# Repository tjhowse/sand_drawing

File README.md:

# Huh?

So you've been reading about all the benefits of this "mindfulness" thing and you want to give it a try.
You do some research and learn it requires "meditation", "introspection" and other kinds of tedious woo.
Who has time for that? It's {current_year} for christ's sake! I don't want a tiny tray of rocks and sand
on my desk to rake around. Surely there's some turn-key solution to this problem already.

That's what this project is for. Outsource responsibility for an ordered mind to make more time for the important things, like computer games. And croissants.

# Oh

This project (will contain/contains) all the knowledge you will need to build your own sand drawing robot. Heavily inspired by the likes of [Sandsara](https://www.kickstarter.com/projects/edcano/sandsara) and [Sisyphus](https://sisyphus-industries.com/). It's a robot that moves a ball around in a bed of sand to draw cool patterns. The patterns can be updated via wifi, and it can cycle through them, you can create your own, etc, etc. This project is open source, cheap, and hopefully as easy as possible to build.

# Building it

## Skills required

This isn't a Lego set. You'll need to have access to the following skills:

* Basic woodworking,
* Intermediate soldering,
* Following technical instructions,
* Drilling a hole sideways through steel rod,
* Recovering from setbacks.

I'll do my best to make the instructions as comprehensive and comphrehensible as I can. I appreciate any and all feedback.

## Videos

[Playlist on Youtube.](https://www.youtube.com/playlist?list=PLT7ckgz8vcoY2YFqqQTA0kUofwehtqQul) Maybe worth watching.

## PCB

The PCB is quite simple and cheap. PCBWay generously sponsored a production run of the v1.2 PCBs and they came out perfect. You can order the PCB using [this link](https://www.pcbway.com/project/shareproject/Sand_Drawing_Robot_control_board_344d0ab2.html) and I'll get a small cut. PCBWay asked me to review the board in a youtube video and link it in the readme, but required no further quid pro quo.

## Build logs

For now the build logs are on [my wiki](https://wiki.tjhowse.com/doku.php?id=projects:sand_drawing:overview). Over time they'll morph into actual instructions and end up in this repo.

## Bill of materials

None of these parts are particularly hard to find. Check ebay and whatnot. Try to buy local if you can. It's hard to guess how much it will all cost in total, but I've tried to design everything to be as economical as possible. Excluding the housing I would (very roughly) estimate the BoM to come out to around AUD$200. The housing could be as cheap as AUD$50 (Melamine board, polycarbonate) or as expensive as you want, with lacquered hardwood and tempered glass.

    These bills of material are slightly out of date. Consult the youtube videos.

### Mechanical
| Item | Type | Count | Note |
| ---- | ---- | ----- | ---- |
| Laser cut parts | Various | Many | The current best solution is made from 3mm laser cut plywood. A 3D printed variant is quite possible. |
| Stepper pulley | GT2-20, 12.35mm high | 2 | My steppers had pulleys from the factory. |
| Belt | S2M belt 120mm | 2 | S2M ≈ GT2. |
| Belt | S2M belt 278mm | 1 | |
| Shaft 1 | 8mm x 90mm | 1 | Mild steel is easier to cross-drill than stainless. |
| Shaft 2 | 8mm x 33mm | 1 | |
| Bearing | 608 | 6 | Cheap skate bearings are fine. |
| Washers | 8mm ID, 15.7mm OD | 5 | OD not critical, but it must not rub on outer race of bearings. |
| Washers | 3mm ID, 6.8mm OD | 12 | |
| Bolts | M3x12mm | 8 | I used all 20mm and cut them to length. |
| Bolts | M3x20mm | 2 | |
| Nylock nuts | M3 | 2 | Nylock not critical. |
| Pins | 2mm diameter | 5 | Roll pins would be best, I used nails. +1 extra for pinning shaft 1 into the bearings. |
| Magnets | 12mm diameter, 2mm high neodymium | 2-4 | Situational dimensions. Get a variety of sizes to aid experimentation. |
| Cable ties | 200mm x 4.6mm Nylon | 2 | Dimensions not critical. |

### Electrical
| Item | Type | Count | Note |
| ---- | ---- | ----- | ---- |
| Microcontroller | ESP-WROOM-32D | 1 | Wifi and bluetooth built-in |
| Stepper motor | NEMA-17 | 2 | 200 steps/revolution, around 40mm long, at least 30 N.cm of holding torque. It's not critical, really. |
| Stepper driver | Pololu pinout | 2 | A4988, DRV8825 or TMC2100 in [increasing order of preference](https://github.com/tjhowse/sand_drawing/issues/6) |
| PCB | Custom made | 1 | The design is [here](./pcb/sand_drawing). It's easier and cheaper to have one made than you [might imagine](./pcb/sand_drawing/README_PCB.md).
| Hall effect sensors | SS49E | 2 | Used for detecting arm position. |
| PSU | 12v DC 1A | 1 | A wall wart should be fine. |
| Stepper driver socket | 16x1 2.54mm female | 2 | https://au.rs-online.com/web/p/pcb-sockets/2304893/ |
| Stepper motor socket | 4x1 3.5mm | 2 | https://au.rs-online.com/web/p/pcb-headers/8971039/ |
| Stepper motor plug | 4x1 3.5mm | 2 | https://au.rs-online.com/web/p/pcb-terminal-blocks/8971004/ |
| Optoswitch socket | 3x1 3.5mm | 2 | https://au.rs-online.com/web/p/pcb-headers/8971020/ |
| Optoswitch plug | 3x1 3.5mm | 2 | https://au.rs-online.com/web/p/pcb-terminal-blocks/8971001/ |
| Power socket | 2x1 3.5mm | 1 | https://au.rs-online.com/web/p/pcb-headers/8971026/ |
| Power plug | 2x1 3.5mm | 1 | https://au.rs-online.com/web/p/pcb-terminal-blocks/8970998/ |
| Buttons | 6mm | 2 | https://au.rs-online.com/web/p/tactile-switches/1359534/ |
| UART Header | 3x1 2.54mm male | 1 | https://au.rs-online.com/web/p/pcb-headers/8967364/ |
| 12VDC Barrel socket | 2.1mm pin | 1 | https://au.rs-online.com/web/p/dc-power-sockets/0448370/ |

### Enclosure
| Item | Type | Count | Note |
| ---- | ---- | ----- | ---- |
| Base | Wooood? | 1 | Holds the steppers and circuitry. |
| Top | Wooood? | 1 | Any convex polygon should work. |
| Bed | Glass? | 1 | |
| Lid | Glass | 1 | |
| Sand | Sand | 31378908 | < 100 μm grains, dry.

# Flashing

To flash the software onto the ESP32 you'll need to use the provided scripts `flash32.sh` and `write32.sh`. You'll have to update them with the current version of micropython and the device name of your serial port adapter. When flashing micropython you'll need to hold down the IO0 button while connecting power, then release it five or so seconds after powering on. You can then run `flash32.sh` and it'll write the "OS" onto the chip. Then you can repower again and run `write32.sh` to load the project's scripts onto the board.

# Communication
The ESP-WROOM-32 has wifi and BLE built in. Currently the robot connects to a wifi network, then an MQTT server, to receive commands. Bluetooth should also be possible in the future.

## MQTT Topics
There are a few topics that the robot listens to. Each topic starts with `{secrets.mqtt_root}/sand_drawing/`. I suggest you publish patterns/generators with the retain bit so the robot starts up and then begins that pattern.
| Topic | Example payload | Description |
| ----  | ------- | ----------- |
| `pattern` | `G28 X,G28 Y,G1 X0 Y175,G1 X123 Y123,G1 X175 Y0,J0 2` | Starts drawing the pattern defined by the GCODE in the payload. |
| `generator` | [Here](./pub_gen.py#L82) | Starts drawing the pattern defined by the generator in the payload. See below for details on generators. |
| `save_generator` | `1.pat {generator string}` | Saves the generator to a file in the robot's flash storage. The file extension must be `.pat`. A blank string will erase the generator. |
| `run_generator` | `1.pat` | Starts drawing the previously saved generators. |
| `delete_generator` | `1.pat` | Deletes a generator saved to the robot. |
| `list_generators` | N/A | Publishes a list of filenames to `generator_list` topic. |
| `shuffle_generators` | `3600` | Randomly picks a saved generator and starts drawing it. Optionally provide a number of seconds before choosing another random generator |

# Configuration
There are some files you'll need to edit before your robot will work for you, probably.
[#TODO populate this section.](https://github.com/tjhowse/sand_drawing/issues/13)

# Pattern definition
There are currently two ways to design patterns for the robot.

## GCODEs
This is a sequence of coordinates that define the path of the ball, as well as changing modes and looping. The following GCODES are currently supported. GCODES are separated by a comma.

| Name | GCODE | Example | Description |
| ---- | ----- | ------- | ----------- |
| Home axis| G28 | `G28 X,G28 Y,` | Home either the X or Y axis. Any command that needs an absolute position reference will fail unless both axes have been homed first. |
| Move | G1 | `G1 X10 Y50 S100,` | Go to the X and Y coordinates specified at 100mm/s. Currently the [speed field is ignored](https://github.com/tjhowse/sand_drawing/issues/4). The G1 movement mode carefully tracks every step and should be perfectly accurate if your steppers do not slip. |
| Fast move | G0 |  `G0 X10 Y50 S100,` | Same as G1 however the step signal square wave is generated using PWM so some resolution is lost. At time of writing it is not well-supported. It's really fast though. |
| Coordinate mode | G16 | `G16 0,` | This setting is used to control the interpretation of the `X` and `Y` parameters in the G0 and G1 commands. `0`: Raw speed, `1`: Raw angle, `2`: Cartesian (Default), `3`: Polar (unimplemented) |
| Jump | J0 | `J0 3,` | This jumps to the specified line in the GCODE-defined pattern. Used for creating loops. |
| Absolute coordinate mode | G90 | `G90` | Puts the robot into absolute movement mode. Coordinates in G0/G1 commands are interpreted as absolute position references. (Default) |
| Relative coordinate mode | G91 | `G91` | Puts the robot into relative movement mode. Coordinates in G0/G1 commands are interpreted as movement vectors from the previous position. |

## Generators
You can define a pattern using a python generator function. [Examples here](./pub_gen.py). This is probably the best option for non-trivial patterns.

### Tread lightly
Keep the target hardware in mind when writing generators. It's very resource-constrained. Try to limit RAM usage, and think hard before `import`ing anything. There are some [helper functions](./generator_libs.py) and [constants](./constants.py) in-scope that you can use.

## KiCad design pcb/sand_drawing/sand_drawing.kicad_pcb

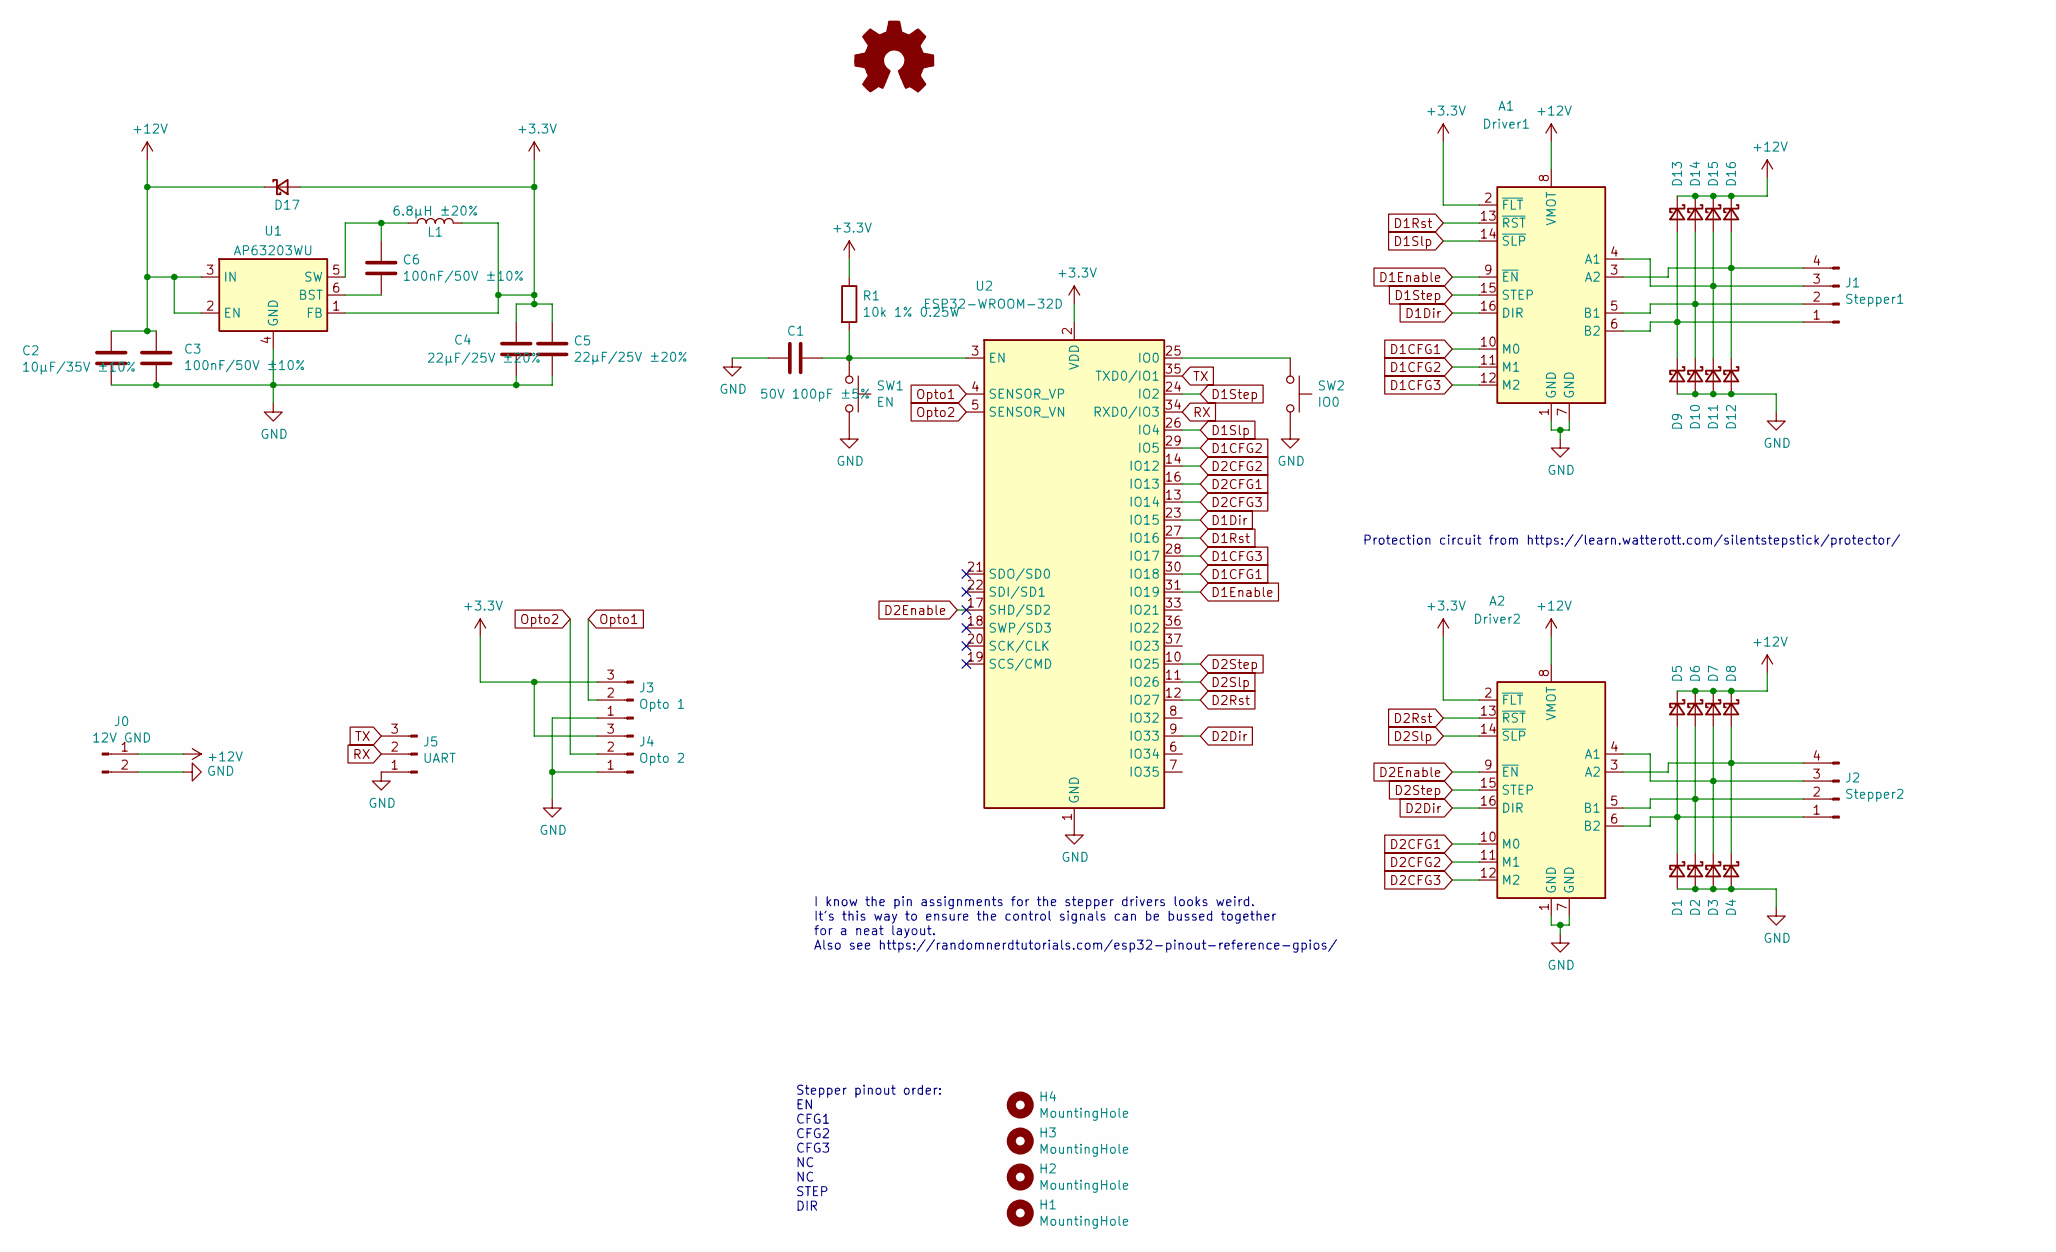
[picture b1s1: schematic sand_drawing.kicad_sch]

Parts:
A1: Driver1; Pololu_Breakout-16_15.2x20.3mm
A2: Driver2; Pololu_Breakout-16_15.2x20.3mm
C1: 50V 100pF ±5%; C_0805_2012Metric; MPN CL21C101JBANNNC; LCSC C1790
C2: 10µF/35V ±10%; C_1206_3216Metric; MPN CGA5L1X7R1V106K160AE; LCSC C15850
C3, C6: 100nF/50V ±10%; C_0603_1608Metric; MPN CGA3E2X7R1H104K080AA; LCSC C15850
C4, C5: 22µF/25V ±20%; C_1206_3216Metric; MPN C3216X5R1E226M160AB; LCSC C15850
D1, D2, D3, D4, D5, D6, D7, D8, D9, D10, D11, D12, D13, D14, D15, D16, D17: 100V 850mV@2A Schottky Diode; D_SMB; MPN Taiwan Semiconductor SS210; LCSC C14996
H1, H2, H3, H4: MountingHole; MountingHole_3.2mm_M3
J0: 12V GND; PhoenixContact_MCV_1,5_2-G-3.5_1x02_P3.50mm_Vertical
J1: Stepper1; PhoenixContact_MCV_1,5_4-G-3.5_1x04_P3.50mm_Vertical
J2: Stepper2; PhoenixContact_MCV_1,5_4-G-3.5_1x04_P3.50mm_Vertical
J3: Opto 1; PhoenixContact_MCV_1,5_3-G-3.5_1x03_P3.50mm_Vertical
J4: Opto 2; PhoenixContact_MCV_1,5_3-G-3.5_1x03_P3.50mm_Vertical
J5: UART; PinSocket_1x03_P2.54mm_Vertical
L1: 6.8µH ±20%; WURTH_6060; MPN Wurth 74439346068
LOGO1: Logo_Open_Hardware_Small; OSHW-Logo2_14.6x12mm_SilkScreen
R1: 10k 1% 0.25W; R_0603_1608Metric; MPN CRGP0603F10K; LCSC C25804
SW1: EN; SW_PUSH_6mm
SW2: IO0; SW_PUSH_6mm
U1: AP63203WU; TSOT-26-6; MPN AP63203WU-7
U2: ESP32-WROOM-32D; ESP32-WROOM-32; MPN ESP32-WROOM-32D

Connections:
+3V3: A1.2 (~FLT), A2.2 (~FLT), C4.1, C5.1, D17.2 (A), J3.3, J4.3, L1.2, R1.1, U1.1 (FB), U2.2 (VDD)
+12V: A1.8 (VMOT), A2.8 (VMOT), C2.1, C3.1, D5.1 (K), D6.1 (K), D7.1 (K), D8.1 (K), D13.1 (K), D14.1 (K), D15.1 (K), D16.1 (K), D17.1 (K), J0.1, U1.2 (EN), U1.3 (IN)
D1CFG1: A1.10 (M0), U2.30 (IO18)
D1CFG2: A1.11 (M1), U2.29 (IO5)
D1CFG3: A1.12 (M2), U2.28 (IO17)
D1Dir: A1.16 (DIR), U2.23 (IO15)
D1Enable: A1.9 (~EN), U2.31 (IO19)
D1Rst: A1.13 (~RST), U2.27 (IO16)
D1Slp: A1.14 (~SLP), U2.26 (IO4)
D1Step: A1.15 (STEP), U2.24 (IO2)
D2CFG1: A2.10 (M0), U2.16 (IO13)
D2CFG2: A2.11 (M1), U2.14 (IO12)
D2CFG3: A2.12 (M2), U2.13 (IO14)
D2Dir: A2.16 (DIR), U2.9 (IO33)
D2Enable: A2.9 (~EN), U2.17 (SHD/SD2)
D2Rst: A2.13 (~RST), U2.12 (IO27)
D2Slp: A2.14 (~SLP), U2.11 (IO26)
D2Step: A2.15 (STEP), U2.10 (IO25)
GND: A1.1 (GND), A1.7 (GND), A2.1 (GND), A2.7 (GND), C1.2, C2.2, C3.2, C4.2, C5.2, D1.2 (A), D2.2 (A), D3.2 (A), D4.2 (A), D9.2 (A), D10.2 (A), D11.2 (A), D12.2 (A), J0.2, J3.1, J4.1, J5.1, SW1.2, SW2.2, U1.4 (GND), U2.1 (GND), U2.15 (GND), U2.38 (GND), U2.39 (GND)
unnamed: A1.4 (A1), D11.1 (K), D15.2 (A), J1.3
unnamed: A1.3 (A2), D12.1 (K), D16.2 (A), J1.4
unnamed: A1.5 (B1), D10.1 (K), D14.2 (A), J1.2
unnamed: A1.6 (B2), D9.1 (K), D13.2 (A), J1.1
unnamed: A2.4 (A1), D3.1 (K), D7.2 (A), J2.3
unnamed: A2.3 (A2), D4.1 (K), D8.2 (A), J2.4
unnamed: A2.5 (B1), D2.1 (K), D6.2 (A), J2.2
unnamed: A2.6 (B2), D1.1 (K), D5.2 (A), J2.1
unnamed: C6.2, U1.6 (BST)
unnamed: C6.1, L1.1, U1.5 (SW)
unnamed: C1.1, R1.2, SW1.1, U2.3 (EN)
unnamed: SW2.1, U2.25 (IO0)
Opto1: J3.2, U2.4 (SENSOR_VP)
Opto2: J4.2, U2.5 (SENSOR_VN)
RX: J5.2, U2.34 (RXD0/IO3)
TX: J5.3, U2.35 (TXD0/IO1)

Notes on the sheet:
Protection circuit from https://learn.watterott.com/silentstepstick/protector/
I know the pin assignments for the stepper drivers looks weird. It's this way to ensure the control signals can be bussed together for a neat layout. Also see https://randomnerdtutorials.com/esp32-pinout-reference-gpios/
Stepper pinout order: EN CFG1 CFG2 CFG3 NC NC STEP DIR

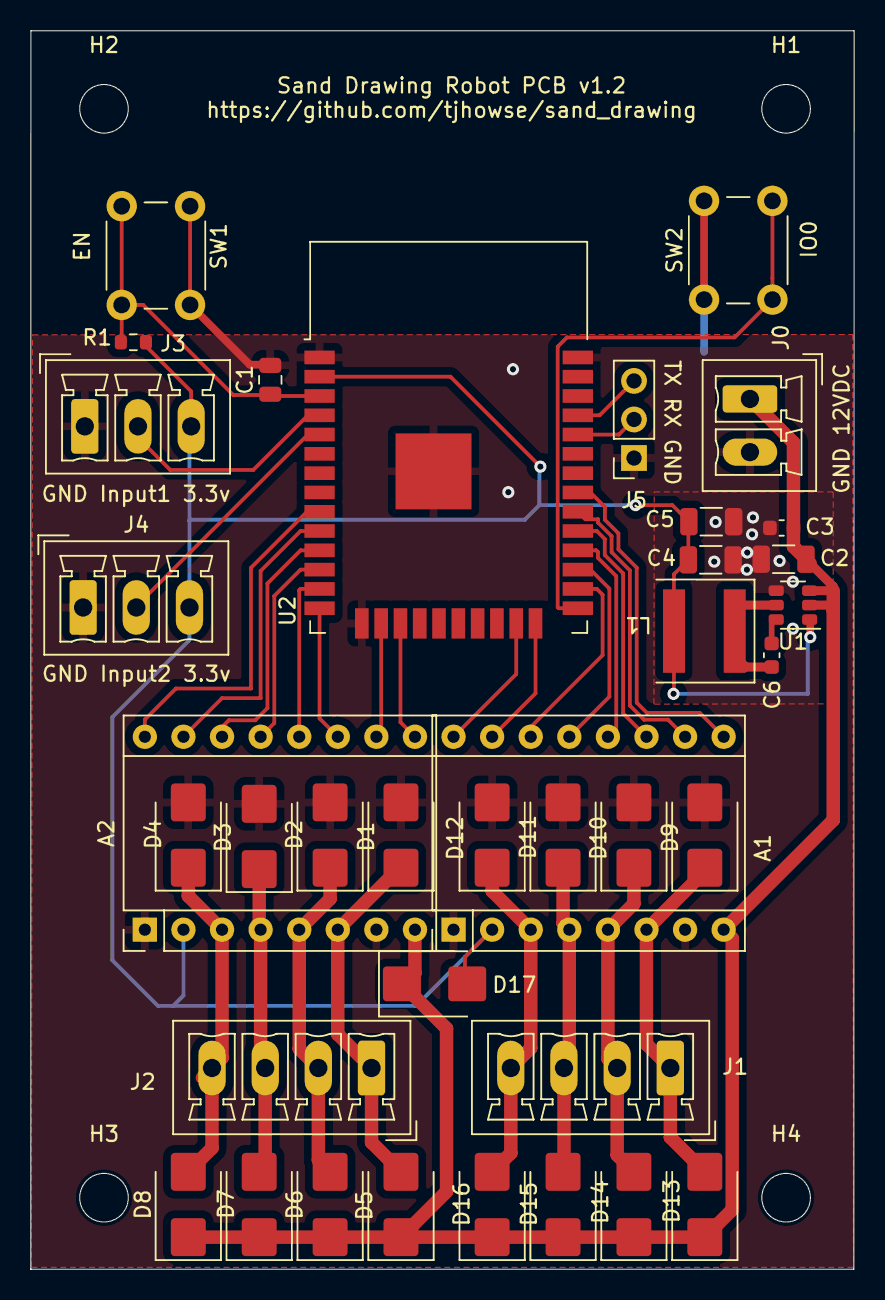
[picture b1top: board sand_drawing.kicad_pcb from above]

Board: 2 copper layers, 54.2 x 81.5 mm, 41 parts (0 on the bottom side), 35 nets.

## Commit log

2020-04-12 More working.
2020-04-12 Add readme, and something else I don't remember.
2020-04-13 Add arm1
2020-04-13 Add a link to the belt length calculator.
2020-04-13 Fix whitespace
2020-04-13 Starting the framework for the code.
2020-04-13 Add a guide to the other side shaft 1 drive gear.
2020-04-13 Fix the split on arm1
    Add shaft 2 driven pulley
2020-04-13 Add bottom bearing mount stuff.
2020-04-14 Make arm slots work better.
2020-04-14 Add framework for mqtt stuff.
2020-04-14 Add gitignore to exclude changes to secrets.py
2020-04-14 Add basic framework for testing steppers.
2020-04-15 Move real secrets to secrets_real.py so I don't accidentally check in my secrets.
2020-04-15 Beef up lip on shaft 2 driven pulley.
    Add arm2
2020-04-15 Add license.
2020-04-15 Start thinking about proper stepper driving.
2020-04-15 Add an assembled view.
    Add optoflags and an optoswitch holder.
2020-04-16 Tweak for printing.
2020-04-16 Add PCB design. Not routed yet.
2020-04-17 Add jumpers for microstepping.
2020-04-17 Rearrange stuff, start routing.
2020-04-18 More traces
2020-04-18 Add flood fills.
    Add silkscreen text for spare pins.
2020-04-18 Tidy up schematic.
2020-04-18 Tweaks.
2020-04-18 Add the basics of some stepper control. Still not working perfectly.
2020-04-19 Rework interval maths.
2020-04-19 Bulk hacking. Home one axis at a time for now.
2020-04-19 Added loads.
2020-04-19 Add debug
    Fix multi-axis movement
    Add easy toggle for wild mode.
2020-04-19 Add debug mode flag for printing debug messages.
2020-04-19 Rotate pin holding arm1 to shaft1 to allow it to be tapped through.
2020-04-19 Fix GH issue #2 by splitting arm1 horizontally not vertically.
2020-04-19 Use the split version of arm1 in the assembled module.
2020-04-21 Lots of float squashing. More debugging. Less debugging sometimes.
2020-04-21 Add receiving patterns from MQTT!
    It only loads a new pattern on stepping between instructions. So patterns with long-lived steps, such as raw relative moves that continue forever, new patterns will never be loaded.
2020-04-23 Working on adding support for an esp32-based device.
2020-04-23 Add a flag to disable MQTT checking, and check for new patterns on a timer.
2020-04-23 Break the PWM stepping out to a setting separate to the microcontroller. This code gets 3.7s revolutions on an ep32.
2020-04-25 Removed the program-wide PWM stepping setting in favour of G0 - Fast move gcode.
    Not fully implemented yet.
2020-04-25 Some refactoring, spam prevention, etc.
2020-04-25 Track index on G0 moves. First test showed this doesn't work quite right.
2020-04-25 Working on handling fast movements overshooting their target by good margins.
2020-04-25 Shockingly broken in most ways.
2020-04-26 Working on stopping a fast move at an ideal point. Not quite there.
2020-05-04 Testing new patterns with DRV8825 stepper drivers.
2020-05-04 Mod 360 the angle to set_angle.
2020-05-04 Split project into multiple files for ease of navigation.
2020-05-04 Working on the kinematics stuff.
2020-05-04 Refactor complete.
2020-05-04 Cartesian mode working, somewhat.
2020-05-05 Working finding the other kinematic solution.
2020-05-05 Finish calculating the most direct movement path between the current and desired position.
2020-05-06 Add logic to slow down arm1 to match the max move speed of arm2.
2020-05-06 Handle the zero case
2020-05-06 Notes on speed calculation, tweaks.
2020-05-06 Better differential speed compensation for cartesian moves. Not perfect yet.
2020-05-10 Added arm2optoarm for homing Y axis.
2020-05-11 Made arm2 a bit thinner to give more clearance for the arm2 opto.
2020-05-12 Allow to home to indicies other than 0.
2020-05-12 Beginning to work on the bounds-limiting code to stop the arm hitting the sides of the enclosure.
    This doesn't work yet. I've added test_coordinate_bounds.py to check things out off-board.
2020-05-12 add a few more test cases.
2020-05-12 Handle import failure better when running off-target.
    Fix demo case.
2020-05-12 Fix closest two points calculation.
2020-05-12 :thonking:
2020-05-12 Remove debugging and truncate filtered coordinates.
2020-05-12 On second thoughts, let's not. That might cause weird stepping along the edges.
2020-05-12 Use the new code to limit the coordinates.
2020-05-12 Fix arm length, fine-tune homing index zero points.
2020-05-12 Add TODO.
2020-05-12 Add resource for maths to solve scara properly.
2020-05-13 Add another URL to read.
2020-05-13 Begin work on segmented moves.
2020-05-13 Camels spit.
2020-05-13 Calculate a stepwise movement vector and move set_angles_for_point logic into its own method.
2020-05-13 Working on intermediate moves.
2020-05-13 Remove commented-out path speed compensation. Probably won't need it.
2020-05-13 Remove split_path_move flag. We can work things out directly without storing that state.
2020-05-13 Only use this movement logic if we're doing cartesian movements.
2020-05-13 Finalise stepwise motion. Disable debug mode.
2020-05-14 Remove G15.
2020-05-14 Use readable descriptions for movement modes in code.
2020-05-14 To generate testing gcode that follows the border of the enclosure.
2020-05-14 Bleh. Bit of a disaster. Trying to improve homing a bit so we're actually at 0,0 after a home.
2020-05-15 Remove a bunch of complexity from the homing logic.
    Still not perfect, but better.
2020-05-15 Setting up pattern generator support woo.
2020-05-15 Woohoo! Generators are working!
2020-05-15 Generators now working!
    Added a note about the generator try/catch bug. Need to document the generator spec now.
2020-05-15 Add a trivial todo because it's late and I can barely even spell 'trivial'
2020-05-16 Add a youtube link to the weird Y axis movement
2020-05-16 Ignore pyc files.
2020-05-16 Add a spirograph pattern and a pattern visualiser.
2020-05-16 Better live-loading of patterns. Not 100% yet.
2020-05-16 Remove stepper.seeking. Default homing to false.
2020-05-16 A fairly substantial rework of homing logic. Should work better now.
2020-05-17 Working on a new pattern generator.
2020-05-17 Finish grid pattern generator
2020-05-17 Re-draw the grid 90 degrees rotated.
2020-05-17 Add a wave pattern generator.
2020-05-17 Add rotating_poly generator. Working on contracting_swirls.
2020-05-17 Slight tweak to contracting_swirls.
2020-05-18 Rejingle the core loop a bit to load new patterns/generators ASAP.
2020-05-18 Basic spiral for clearing the bed.
2020-05-18 Christ I hope this reads as satire.
2020-05-19 More docs.
2020-05-19 Add link to youtube videos.
2020-05-19 Add the GCODE spec into a table.
2020-05-19 More readme love.
2020-05-19 Clarify communications.
2020-05-19 More readme.
2020-05-19 Add a readme specific to the PCB.
2020-05-19 Start the work involved in transitioning to the ESP-WROOM-32D and TMC2100.
2020-05-20 Readme tweak.
2020-05-22 More work on adding the esp32 .
2020-05-22 Add relative coordinate mode.
2020-05-22 Strip out some noisy debug.
2020-05-22 Update readme to reflect relative moves are now supported.
2020-05-22 Ensure various modes are in their default state when a new pattern or generator starts.
2020-05-22 Add a section on MQTT topics to the readme.
2020-05-22 Refactor topic subscriptions a bit for better expandability.
2020-05-22 Starting to work on saving, loading and shuffling generators.
2020-05-22 Add random generator shuffling. Untested.
2020-05-22 More tweak.
2020-05-23 Add a bunch of generator loading/saving/shuffling features.
    Not really happy about the use of globals here. Oh well.
2020-05-23 Ignore stl and pyc files.
2020-05-24 Add a new pattern.
2020-05-24 Add vector2.rotate.
2020-05-24 Add some more patterns. Not entirely happy with publish_circle_grid yet.
2020-05-25 Allow access to a vector2's x and y members with an index, so vector2s can be used as tuplealikes.
2020-05-25 Add setitem operator overload to vector2 too.
2020-05-25 Start on a new pattern. Concentric expanding circles from random points until it hits the edge. Maybe stop when it hits an existing circle?
2020-05-25 Add a requirements file. I thought I already had one?
2020-05-25 Tweak starting radius on spirals.
2020-05-25 Avoid starting drawing a circle near the centre.
2020-05-26 Redesigned for ESP32 and TMC2100s. Lots more work to go.
2020-05-27 Not sure what this does.
2020-05-28 Assigning JLCPCB parts store codes to stuff.
2020-05-28 Finished hooking up the EN and IO0 buttons.
2020-05-28 Fix weird link count issue on my desktop...
2020-05-28 Update BOM and beginning to lay out the new PCB.
2020-05-28 Protection diodes placed.
2020-05-29 Nearly finished PCB layout.
2020-05-29 More or less done. It needs to be a bit narrower, so I'm going to rejig the mounting holes.
2020-05-30 Final tweaks. v1.0 PCB done!
2020-05-30 Update electrical BOM in main readme.
2020-05-30 Add code blocks to PCB readme.
2020-05-30 Do line references work in relative paths in readmes?
2020-05-30 Add a link to SIP header socket.
2020-05-30 Add a link to buy SIP header.
2020-05-30 Add clarification to BOM.
2020-05-30 Add some vague budget numbers to the BOM.
2020-05-30 Docs.
2020-05-30 Starting work on a new and cooler spirograph generator.
2020-05-31 Add a better spirograph generator.
2023-10-02 Notes and tweaks
2023-10-04 fixe
2023-10-04 PCB updates, stepper control changes.
2023-10-04 Disable arm 2 while homing arm 1
2023-10-04 Fixes
2023-10-04 Typo
2023-10-07 Force a home on startup before receiving patterns.
2023-10-08 Lasercut version
2023-10-08 Tweaks
2023-10-10 Lasercut stuff work.
2023-10-10 Merge
2023-10-10 add todo
2023-10-10 Add kerf to top holder
2023-10-11 Automate dxf export
2023-10-15 Stuff
2023-10-15 Add belt splitter
2023-10-15 Add requirements for make.py
2023-10-15 Add image to readme.
2023-10-15 Getting there
2023-10-15 Adjustable lasercut arm1
2023-10-18 Minor pin changes
2023-10-18 Enclosure work.
2023-10-18 Use 12 pins for outer ring.
2023-10-18 More enclosure work.
2023-10-18 Add a reasonably silly flexure idea on arm1
2023-10-18 A somewhat more promsing flexure design.
2023-10-18 Flexure tweaks
2023-10-19 Fiddling
2023-10-21 Add bed and stuff.
2023-10-22 Fix bed and felt exports
2023-10-22 PCB notes
2023-10-22 Update PCB and schematic to map all stepper control pins to GPIO.
2023-10-22 Remove backups
2023-10-23 Add hall effect homing sensors
2023-10-24 Update constants for new enclosure.
2023-10-25 Move this file to avoid numpy problems.
2023-10-25 Refactor generator publisher. Increase max diameter to match new enclosure.
2023-10-25 Experiments with chatgpt generated patterns
2023-10-25 Working on new vreg
2023-10-29 v1.1 of the PCB nearly done.
2023-10-29 Update docs
2023-10-30 Updated to kicad v7.0.8.
2023-10-30 Update footprints.
2023-12-11 Add DXFs for lasercut design.
2024-10-05 Minor tweaks to PCB. Thicker 12v rail, rearranged 3.3v connection to drivers, thicker connection between PSU and inductor.
2024-10-06 PCB v1.1
2024-10-06 Tweaks to PCB. Finding parts.
2024-10-06 Updated part numbers and footprints.
2024-10-31 Updated DXFs
2024-10-31 Add esp32 helper scripts.
2024-10-31 Add flashing instructions to readme.
2024-10-31 Cleanup, adding stepper pin config.
2024-10-31 Config for board v1.2
2024-10-31 PCB DRC and label fixes.
2024-10-31 Update pins
2024-11-01 Add notes to readme, bump version number in schematic drawing, add PCB changelog.
2024-11-01 Update PCB readme.
2024-11-01 Remove old BoM, add note to readme.
2024-11-04 Set up pin config.
2024-11-04 More readme updates.
